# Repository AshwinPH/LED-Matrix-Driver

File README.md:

# LED Dot Matrix Driver
Driver circuit and software for a 12 pin 5x7 LED matrix using the Arduino (Elegoo) MEGA 2560
Developed in Arduino ecosystem

## Parts List
All electronics components are included in [Parts List.xlsx](https://github.com/AshwinPH/LED-Matrix-Driver)

* Arduino MEGA (or equivalent) x1
* Breadboard + Jumper wires
  * OR custom circuit board (WIP)
* Transistor x7
* Resistor A x7
* Resistor B x7
* Terminal Blocks x2 (only w/ PCB)

## Wiring
(WIP)

## Setup

All digital pins will work for all 12 pins, don't forget to change pin definitions AND arduino pin assignments

Pin Assignments (not necessarily default)

Pin Definitions (not necessarily default)

Empty PCB

Assembly with components and wiring

(WIP)

Videos of the borad and software in action

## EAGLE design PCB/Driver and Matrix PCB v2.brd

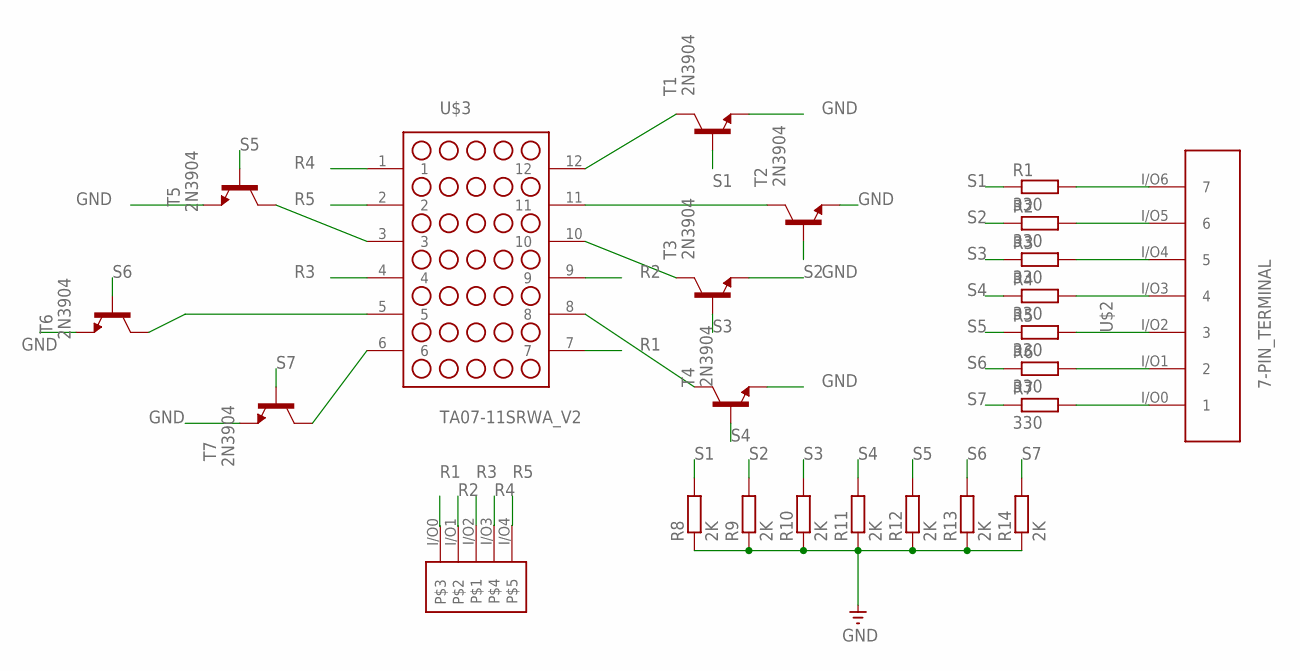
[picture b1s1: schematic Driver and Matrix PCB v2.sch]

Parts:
GND1: GND
R1, R2, R3, R4, R5, R6, R7: 330; 0207/10
R8, R9, R10, R11, R12, R13, R14: 2K; 0207/12
T1, T2, T3, T4, T5, T6, T7: 2N3904; TO92
U$1: 5-PIN_TERMINAL
U$2: 7-PIN_TERMINAL
U$3: TA07-11SRWA_V2

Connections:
GND: GND1.P$1, R8.1, R9.1, R10.1, R11.1, R12.1, R13.1, R14.1, T1.3 (E), T2.3 (E), T3.3 (E), T4.3 (E), T5.3 (E), T6.3 (E), T7.3 (E)
unnamed: R1.2, U$2.I/O6 (7)
unnamed: R2.2, U$2.I/O5 (6)
unnamed: R3.2, U$2.I/O4 (5)
unnamed: R4.2, U$2.I/O3 (4)
unnamed: R5.2, U$2.I/O2 (3)
unnamed: R6.2, U$2.I/O1 (2)
unnamed: R7.2, U$2.I/O0 (1)
unnamed: T7.1 (C), U$3.6
unnamed: T6.1 (C), U$3.5
unnamed: T5.1 (C), U$3.3
unnamed: T4.1 (C), U$3.8
unnamed: T3.1 (C), U$3.10
unnamed: T2.1 (C), U$3.11
unnamed: T1.1 (C), U$3.12
R1: U$1.I/O0, U$3.7
R2: U$1.I/O1, U$3.9
R3: U$1.I/O2, U$3.4
R4: U$1.I/O3, U$3.1
R5: U$1.I/O4, U$3.2
S1: R1.1, R8.2, T1.2 (B)
S2: R2.1, R9.2, T2.2 (B)
S3: R3.1, R10.2, T3.2 (B)
S4: R4.1, R11.2, T4.2 (B)
S5: R5.1, R12.2, T5.2 (B)
S6: R6.1, R13.2, T6.2 (B)
S7: R7.1, R14.2, T7.2 (B)

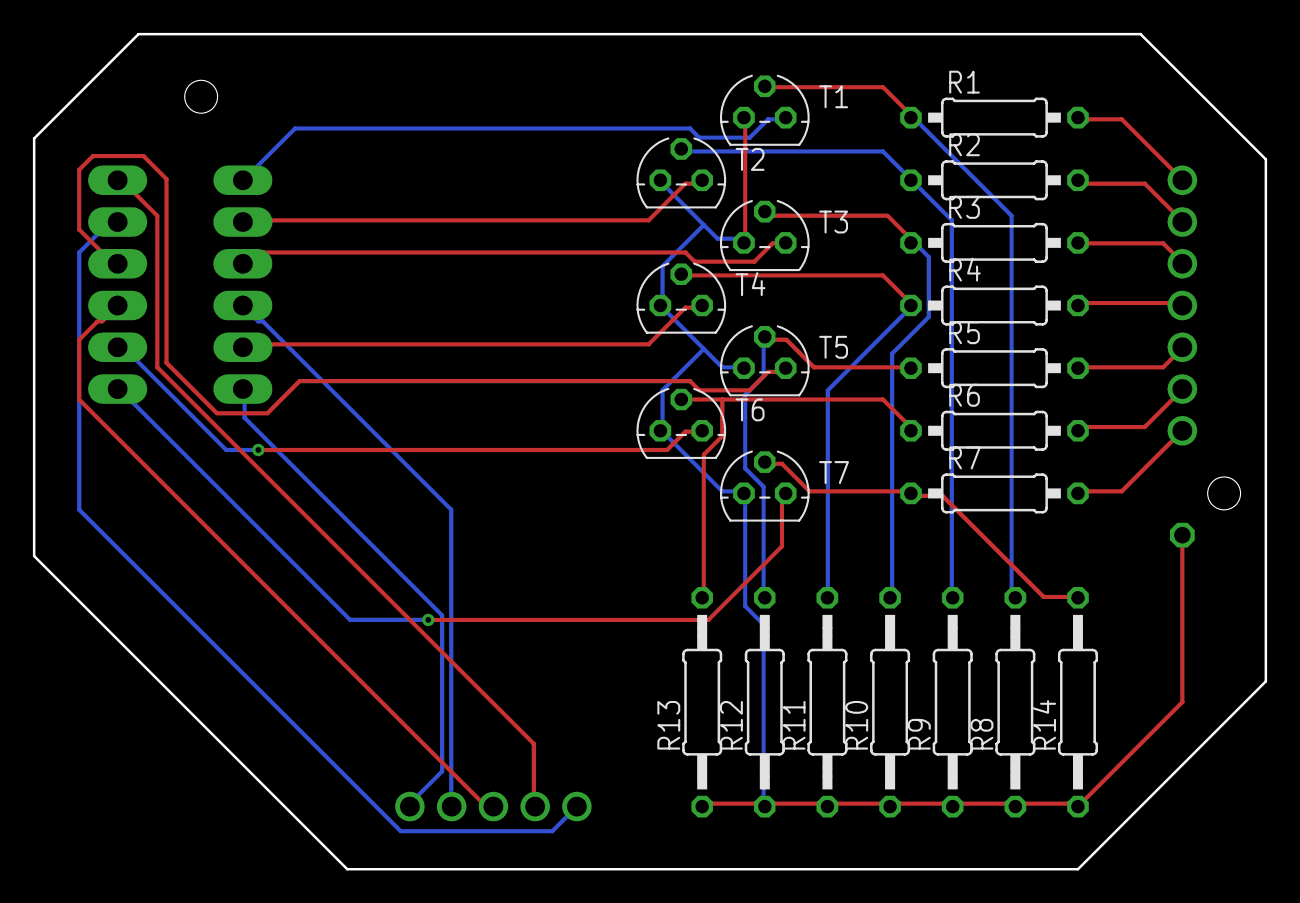
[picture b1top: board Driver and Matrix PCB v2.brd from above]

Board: 2 copper layers, 74.9 x 50.8 mm, 25 parts (0 on the bottom side), 27 nets.

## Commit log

2020-08-25 Create Driver Software v1
2021-09-18 Added Demo Video
2021-09-18 Fixed video link
2021-09-18 Fixed demo link
2021-09-18 Added Scrolling Text Demo
2021-09-18 Added second demo vid

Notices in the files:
parts and their libraries:
supply0: Copyright (C) 2007, Bob Starr
